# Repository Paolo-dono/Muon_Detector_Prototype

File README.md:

# Muon Detector Prototype
PCB design for the microcontroller subsystem of a muon detector.
- Creator: Paolo de Bruyn
- License: GNU General Public License v3.0

NOTE: Although the name of the project folder is STM32WL55JC_pcb_design, the STM32WL55JC is not the microcontroller that is used in the design. It was used during the initial design, but it has been replaced by the STM32F051R8. The reason why it was not renamed was because all the external component libraries that were added use the absolute filepath, and it would be a mission to change all of them.

## Component availability
All of the components are available from JLCPCB except for a few exceptions.

The GPS module needs an external antenna in order to function properly. Any antenna that has an IPEX MHF connector can be used. One recommendation is the KYOCERA AVX GPS Antenna 1004138 which is available from RS Components.

The banana connectors are sadly not available from JLCPCB but can be procured from DigiKey. It is recommended that the CT3151SP-0 connector is ordered for the ground connector as it is black, and the CT3151-6 is a blue connector which can be used for the supply voltage.

## Using the project
Simply clone the project and open it in KiCAD. The PCB should be in a state where it can already be printed by JLCPCB, but if not, probably only minor changes will have to be made.

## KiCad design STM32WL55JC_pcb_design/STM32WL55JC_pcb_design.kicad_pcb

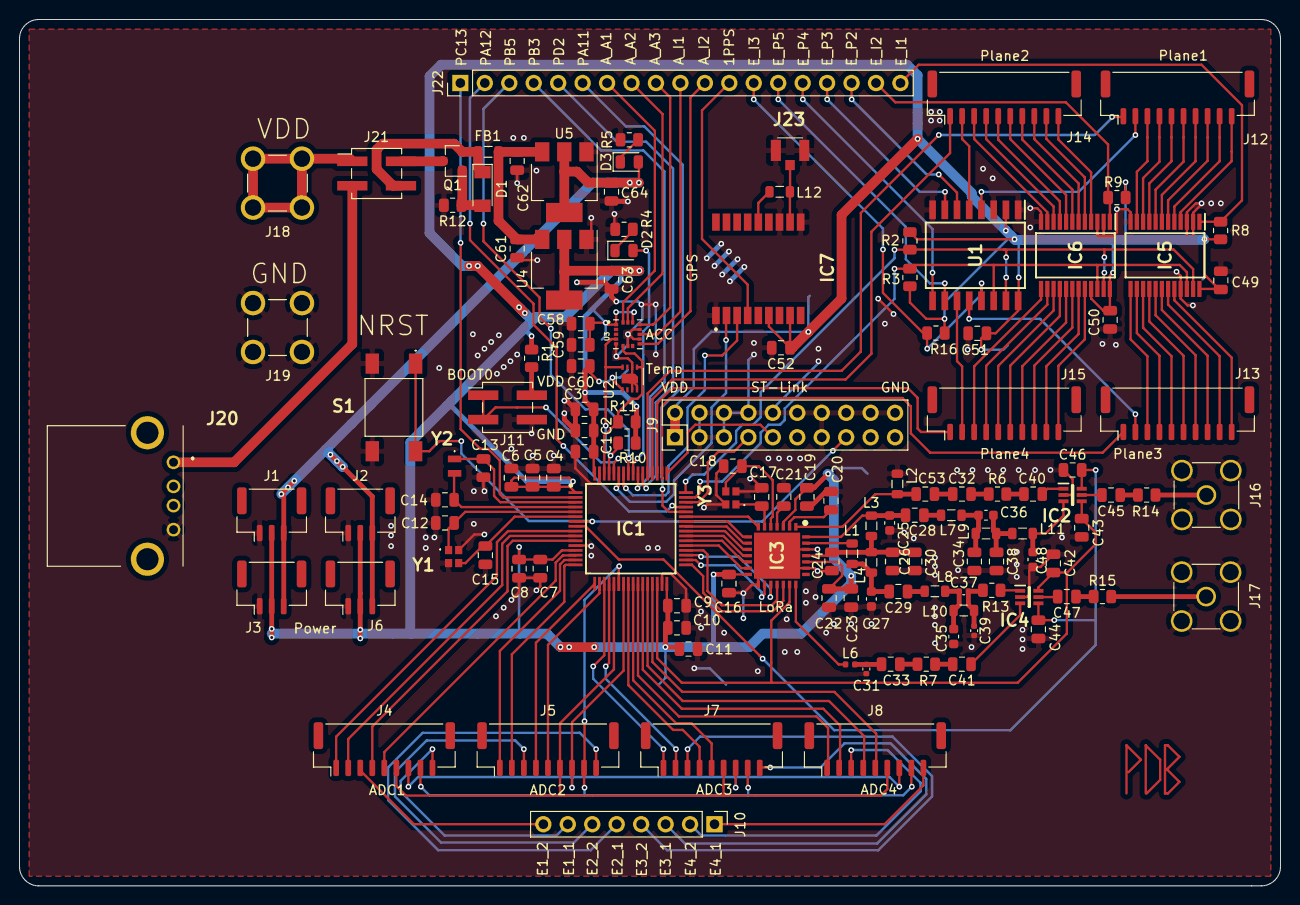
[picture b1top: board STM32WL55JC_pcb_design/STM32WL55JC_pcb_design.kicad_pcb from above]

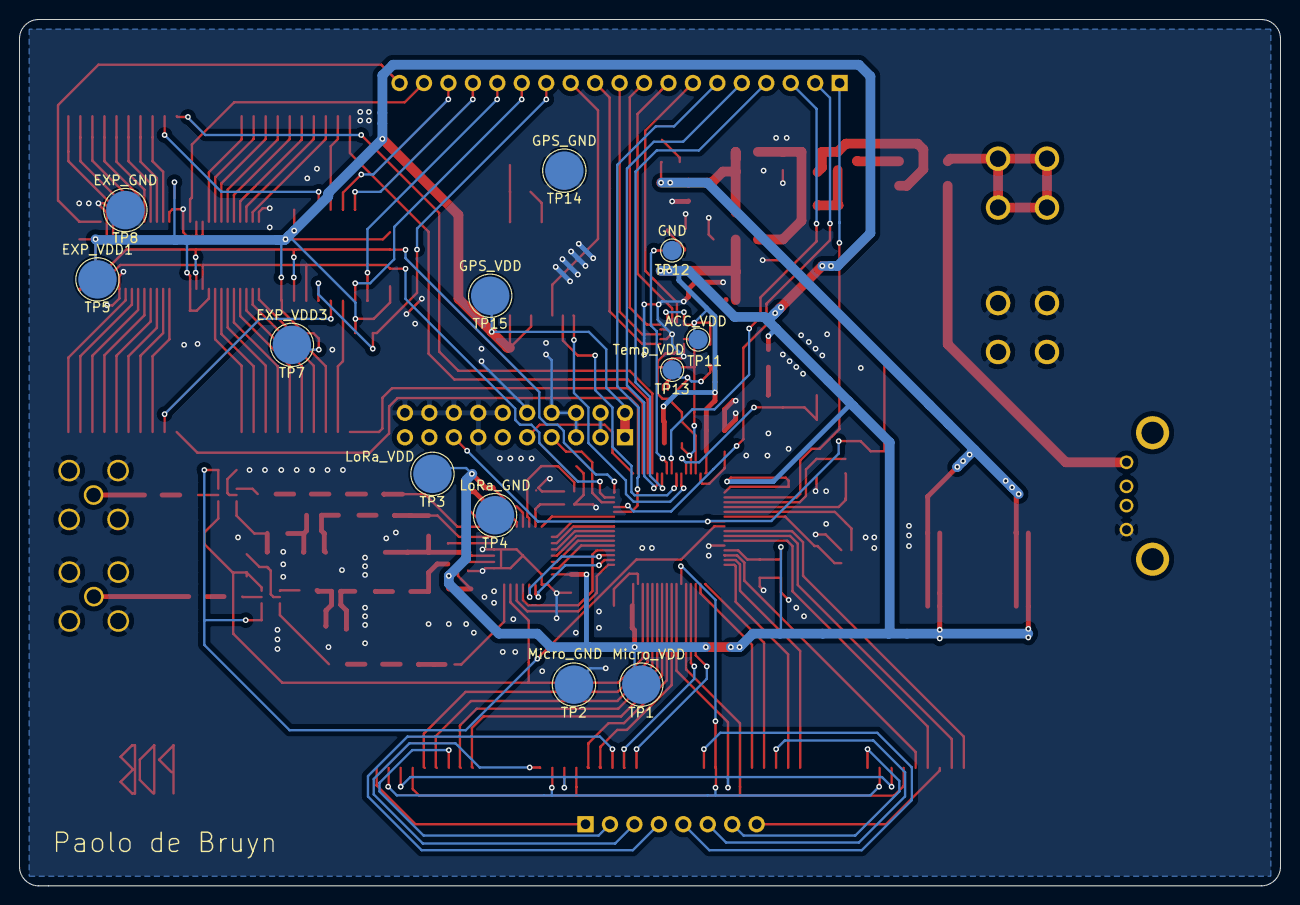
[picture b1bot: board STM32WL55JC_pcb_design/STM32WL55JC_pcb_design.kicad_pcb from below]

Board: 2 copper layers, 131.0 x 90.0 mm, 143 parts (12 on the bottom side), 160 nets.

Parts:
C1, C2, C4, C5, C9, C10, C16, C19, C20, C21, C23, C49, C50, C51, C58, C60: 100nF; C_0805_2012Metric
C3, C6, C11: 4.7uF; C_0805_2012Metric
C7, C24: 10nF; C_0805_2012Metric
C8: 1uF; C_0805_2012Metric
C12, C15, C17, C18: 10pF; C_0805_2012Metric
C13, C14, C34: 15pF; C_0805_2012Metric
C22, C28, C30, C32, C33, C41, C45, C47: 47pF; C_0805_2012Metric
C25, C27, C35: 8.2pF; C_0603_1608Metric
C26: 100pF; C_0805_2012Metric
C29: 22pF; C_0805_2012Metric
C31, C39: 3.3pF; C_0402_1005Metric
C36: 2.7pF; C_0603_1608Metric
C37: 1.5pF; C_0402_1005Metric
C38: 12pF; C_0805_2012Metric
C40: 47nF; C_0805_2012Metric
C42: 4.7pF; C_0603_1608Metric
C43, C44, C46, C48: 1nF; C_0805_2012Metric
C52, C59, C61, C62, C63, C64: 10uF; C_0805_2012Metric
C53: 4.7pF; C_0805_2012Metric
D1: ZMM3V3; D_MiniMELF
D2, D3: LED; LED_0805_2012Metric
FB1: 100@100MHz; L_0805_2012Metric
IC1: STM32F051R8T6; QFP50P1200X1200X160-64N
IC2, IC4: CG2409M2; CKRF2406XS03-C2
IC3: SX1276IMLTRT; QFN65P600X600X100-29N
IC5, IC6: PCF8575TS_1,118; SOP65P775X200-24N
IC7: ATGM336H-5N31; ATGM336H5N31
J1, J2, J3, J6: Conn_01x03; JST_GH_BM03B-GHS-TBT_1x03-1MP_P1.25mm_Vertical
J4, J5, J7, J8: Conn_01x09; JST_GH_BM09B-GHS-TBT_1x09-1MP_P1.25mm_Vertical
J9: Conn_02x10_Odd_Even; PinHeader_2x10_P2.54mm_Vertical
J10: Conn_01x08_Male; PinHeader_1x08_P2.54mm_Vertical
J11, J21: Conn_02x02_Odd_Even; PinHeader_2x02_P2.54mm_Vertical_SMD
J12, J13, J14, J15: Conn_01x10; JST_GH_BM10B-GHS-TBT_1x10-1MP_P1.25mm_Vertical
J16, J17: Conn_Coaxial; SMA_Amphenol_901-144_Vertical
J18, J19: CT3151-2; CALTEST_CT3151-2
J20: USB-A-S-F-B-TH; USBASFBTH
J22: Conn_01x19_Male; PinHeader_1x19_P2.54mm_Vertical
J23: RSP-122811-01; RSP12281101
L1: 2.2nH; L_0805_2012Metric
L2, L11: 18nH; L_0805_2012Metric
L3, L12: 47nH; L_0805_2012Metric
L4: 33nH; L_0805_2012Metric
L6: 10nH; L_0402_1005Metric
L7: 22nH; L_0805_2012Metric
L8: 5.6nH; L_0805_2012Metric
L9: 12nH; L_0805_2012Metric
L10: 4.7nH; L_0805_2012Metric
Q1: AO3401A; SOT-23
R1, R4, R5: 1k; R_0805_2012Metric
R2, R3, R8, R9, R10, R11, R16: 2.2k; R_0805_2012Metric
R6, R7, R13, R14, R15: 0R; R_0805_2012Metric
R12: 100kOhm; R_0805_2012Metric
S1: TL3301AF160QJ
TP1: Micro_VDD; TestPoint_Pad_D4.0mm
TP2: Micro_GND; TestPoint_Pad_D4.0mm
TP3: LoRa_VDD; TestPoint_Pad_D4.0mm
TP4: LoRa_GND; TestPoint_Pad_D4.0mm
TP5: EXP_VDD1; TestPoint_Pad_D4.0mm
TP7: EXP_VDD3; TestPoint_Pad_D4.0mm
TP8: EXP_GND; TestPoint_Pad_D4.0mm
TP11: ACC_VDD; TestPoint_Pad_D2.0mm
TP12: GND; TestPoint_Pad_D2.0mm
TP13: Temp_VDD; TestPoint_Pad_D2.0mm
TP14: GPS_GND; TestPoint_Pad_D4.0mm
TP15: GPS_VDD; TestPoint_Pad_D4.0mm
U1: PCF8574; SOIC127P1032X265-16N
U2: SHT30-DIS; Sensirion_DFN-8-1EP_2.5x2.5mm_P0.5mm_EP1.1x1.7mm
U3: LIS3DHTR; XDCR_LIS3DHTR
U4: AMS1117-3.3; SOT-223-3_TabPin2
U5: AMS1117-5.0; SOT-223-3_TabPin2
Y1, Y3: 32MHz; NX2016SA32MEXS00ACS06465
Y2: 32.768kHz; SC20S125PF20PPM

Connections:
5V: C64.1, D3.2, J1.3, J2.3, J3.3, J6.3, U5.2
+5V: J20.1, J21.3
ACC_ADC1: J22.7, U3.16
ACC_ADC2: J22.8, U3.15
ACC_ADC3: J22.9, U3.13
ACC_INT1: J22.10, U3.11
ACC_INT2: J22.11, U3.9
ADC_CNVST1_1: IC1.11, J4.4
ADC_CNVST1_2: IC1.9, J4.1
ADC_CNVST2_1: IC1.17, J5.4
ADC_CNVST2_2: IC1.15, J5.1
ADC_CNVST3_1: IC1.24, J7.4
ADC_CNVST3_2: IC1.19, J7.1
ADC_CNVST4_1: IC1.28, J8.4
ADC_CNVST4_2: IC1.26, J8.1
ADC_CS1_1: IC1.14, J4.5
ADC_CS1_2: IC1.10, J4.2
ADC_CS2_1: IC1.18, J5.5
ADC_CS2_2: IC1.16, J5.2
ADC_CS3_1: IC1.25, J7.5
ADC_CS3_2: IC1.20, J7.2
ADC_CS4_1: IC1.29, J8.5
ADC_CS4_2: IC1.27, J8.2
ADC_DIN: IC1.23, J4.7, J5.7, J7.7, J8.7
ADC_DOUT: IC1.22, J4.8, J5.8, J7.8, J8.8
ADC_EOC1_1: J4.9, J10.7
ADC_EOC1_2: J4.3, J10.8
ADC_EOC2_1: J5.9, J10.5
ADC_EOC2_2: J5.3, J10.6
ADC_EOC3_1: J7.9, J10.3
ADC_EOC3_2: J7.3, J10.4
ADC_EOC4_1: J8.9, J10.1
ADC_EOC4_2: J8.3, J10.2
ADC_SCLK: IC1.21, J4.6, J5.6, J7.6, J8.6
BOOT0: IC1.60, J11.1, J11.3
ENC1_1: IC5.4, J12.10
ENC1_2: IC5.5, J12.9
ENC1_3: IC5.6, J12.8
ENC1_4: IC5.7, J12.7
ENC2_1: IC5.8, J12.6
ENC2_2: IC5.9, J12.5
ENC2_3: IC5.10, J12.4
ENC2_4: IC5.11, J12.3
ENC3_1: IC6.4, J14.10
ENC3_2: IC6.5, J14.9
ENC3_3: IC6.6, J14.8
ENC3_4: IC6.7, J14.7
ENC4_1: IC6.8, J14.6
ENC4_2: IC6.9, J14.5
ENC4_3: IC6.10, J14.4
ENC4_4: IC6.11, J14.3
ENC5_1: IC5.20, J13.10
ENC5_2: IC5.19, J13.9
ENC5_3: IC5.18, J13.8
ENC5_4: IC5.17, J13.7
ENC6_1: IC5.16, J13.6
ENC6_2: IC5.15, J13.5
ENC6_3: IC5.14, J13.4
ENC6_4: IC5.13, J13.3
ENC7_1: IC6.20, J15.10
ENC7_2: IC6.19, J15.9
ENC7_3: IC6.18, J15.8
ENC7_4: IC6.17, J15.7
ENC8_1: IC6.16, J15.6
ENC8_2: IC6.15, J15.5
ENC8_3: IC6.14, J15.4
ENC8_4: IC6.13, J15.3
ENC_RST_1: J12.2, U1.4
ENC_RST_2: J14.2, U1.5
ENC_RST_3: J13.2, U1.12
ENC_RST_4: J15.2, U1.11
EXP_INT1: IC5.1, J22.19, R8.2
EXP_INT2: IC6.1, J22.18, R9.2
EXP_INT3: J22.13, R16.2, U1.13
EXP_P2: J22.17, U1.6
EXP_P3: J22.16, U1.7
EXP_P4: J22.15, U1.9
EXP_P5: J22.14, U1.10
EXP_SCL: IC1.47, IC5.22, IC6.22, R3.2, U1.14
EXP_SDA: IC1.48, IC5.23, IC6.23, R2.2, U1.15
GNDREF: C1.2, C2.2, C3.2, C4.2, C5.2, C6.2, C7.2, C8.2, C9.2, C10.2, C11.2, C12.2, C13.2, C14.2, C15.2, C16.2, C17.2, C18.2, C19.2, C20.2, C21.2, C22.2, C23.2, C24.2, C25.2, C26.2, C27.2, C30.2, C31.2, C34.2, C35.2, C38.2, C39.2, C42.2, C43.2, C44.2, C46.2, C48.2, C49.2, C50.2, C51.2, C52.2, C58.1, C59.1, C60.2, C61.2, C62.2, C63.2, C64.2, IC1.12, IC1.31, IC1.63, IC2.2, IC3.15, IC3.23, IC3.26, IC3.29, IC4.2, IC5.2, IC5.3, IC5.12, IC5.21, IC6.2, IC6.3, IC6.12, IC7.1, IC7.10, IC7.12, J1.1, J2.1, J3.1, J6.1, J9.3, J9.4, J9.5, J9.6, J9.8, J9.10, J9.12, J9.13, J9.14, J9.16, J9.18, J9.20, J11.4, J16.2, J17.2, J19.1, J19.2, J19.3, J19.4, J20.4, J23.2, J23.3, L2.1, R4.1, R5.2, R12.2, S1.3, S1.4, TP2.1, TP4.1, TP8.1, TP12.1, TP14.1, U1.1, U1.3, U1.8, U2.2, U2.7, U2.8, U2.9, U3.5, U3.7, U3.10, U3.12, U4.1, U5.1, Y1.2, Y1.4, Y3.2, Y3.4
GPS_1PPS: IC7.4, J22.12
LoRa_DO0: IC1.42, IC3.8
LoRa_DO1: IC1.41, IC3.9
LoRa_DO2: IC1.40, IC3.10
LoRa_DO3: IC1.39, IC3.11
LoRa_DO4: IC1.38, IC3.12
LoRa_DO5: IC1.37, IC3.13
LoRa_MISO: IC1.35, IC3.17
LoRa_MOSI: IC1.36, IC3.18
LoRa_NRST: IC1.43, IC3.7
LoRa_NSS: IC1.33, IC3.19
LoRa_RX_EN: C44.1, C46.1, IC1.8, IC2.6, IC4.4
LoRa_SCK: IC1.34, IC3.16
LoRa_TX_EN: C43.1, C48.1, IC1.30, IC2.4, IC3.20, IC4.6
NRST: IC1.7, J9.15, S1.1, S1.2
unnamed: C17.1, IC3.6, Y3.1
unnamed: C18.1, IC3.5, Y3.3
unnamed: C20.1, IC3.2
unnamed: C21.1, IC3.4
unnamed: C24.1, C26.1, C30.1, IC3.25, L3.1, L4.2
unnamed: C25.1, C28.2, IC3.28, L3.2
unnamed: C27.1, C29.2, L1.1, L4.1
unnamed: C28.1, L7.1
unnamed: C29.1, L8.1
unnamed: C31.1, C33.2, L6.2
unnamed: C32.1, R6.1
unnamed: C32.2, C53.1
unnamed: C33.1, R7.1
unnamed: C34.1, C36.2, L7.2, L9.1
unnamed: C35.1, C37.2, L8.2, L10.1
unnamed: C36.1, C38.1, L9.2, L11.1
unnamed: C37.1, C39.1, L10.2, R13.1
unnamed: C40.1, IC2.1
unnamed: C40.2, R6.2
unnamed: C41.1, IC4.3
unnamed: C41.2, R7.2
unnamed: C42.1, IC2.3, L11.2
unnamed: C45.1, R14.1
unnamed: C45.2, IC2.5
unnamed: C47.1, R15.1
unnamed: C47.2, IC4.5
unnamed: C53.2, IC3.1, L2.2
unnamed: C61.1, C62.1, FB1.1, U4.3, U5.3
unnamed: D1.1, FB1.2, J21.4, Q1.2
unnamed: D1.2, Q1.1, R12.1
unnamed: D2.1, R4.2
unnamed: D2.2, IC1.56
unnamed: D3.1, R5.1
unnamed: IC3.21, L6.1
unnamed: IC3.27, L1.2
unnamed: IC4.1, R13.2
unnamed: IC7.11, J23.1, L12.2
unnamed: IC7.14, L12.1
unnamed: J11.2, R1.2
unnamed: J16.1, R14.2
unnamed: J17.1, R15.2
unnamed: J18.1, J18.2, J18.3, J18.4, J21.1
unnamed: J21.2, Q1.3
OR1: IC1.53, J12.1
OR2: IC1.52, J14.1
OR3: IC1.50, J13.1
OR4: IC1.51, J15.1
OSC32_IN: C13.1, IC1.3, Y2.1
OSC32_OUT: C14.1, IC1.4, Y2.2
OSC_IN: C12.1, IC1.5, Y1.1
OSC_OUT: C15.1, IC1.6, Y1.3
PA11: IC1.44, J22.6
PA12: IC1.45, J22.2
PB3: IC1.55, J22.4
PB5: IC1.57, J22.3
PC13: IC1.2, J22.1
PD2: IC1.54, J22.5
RX: IC1.58, IC7.3
SCL: IC1.61, R10.2, U2.4, U3.4
SDA: IC1.62, R11.2, U2.1, U3.6
SWCLK: IC1.49, J9.9
SWDIO: IC1.46, J9.7
TX: IC1.59, IC7.2
VDD: C1.1, C2.1, C3.1, C4.1, C5.1, C6.1, C7.1, C8.1, C9.1, C10.1, C11.1, C16.1, C19.1, C22.1, C23.1, C49.1, C50.1, C51.1, C52.1, C58.2, C59.2, C60.1, C63.1, IC1.1, IC1.13, IC1.32, IC1.64, IC3.3, IC3.14, IC3.24, IC5.24, IC6.21, IC6.24, IC7.6, IC7.8, J1.2, J2.2, J3.2, J6.2, J9.1, J9.2, R1.1, R2.1, R3.1, R8.1, R9.1, R10.1, R11.1, R16.1, TP1.1, TP3.1, TP5.1, TP7.1, TP11.1, TP13.1, TP15.1, U1.2, U1.16, U2.5, U3.1, U3.14, U4.2

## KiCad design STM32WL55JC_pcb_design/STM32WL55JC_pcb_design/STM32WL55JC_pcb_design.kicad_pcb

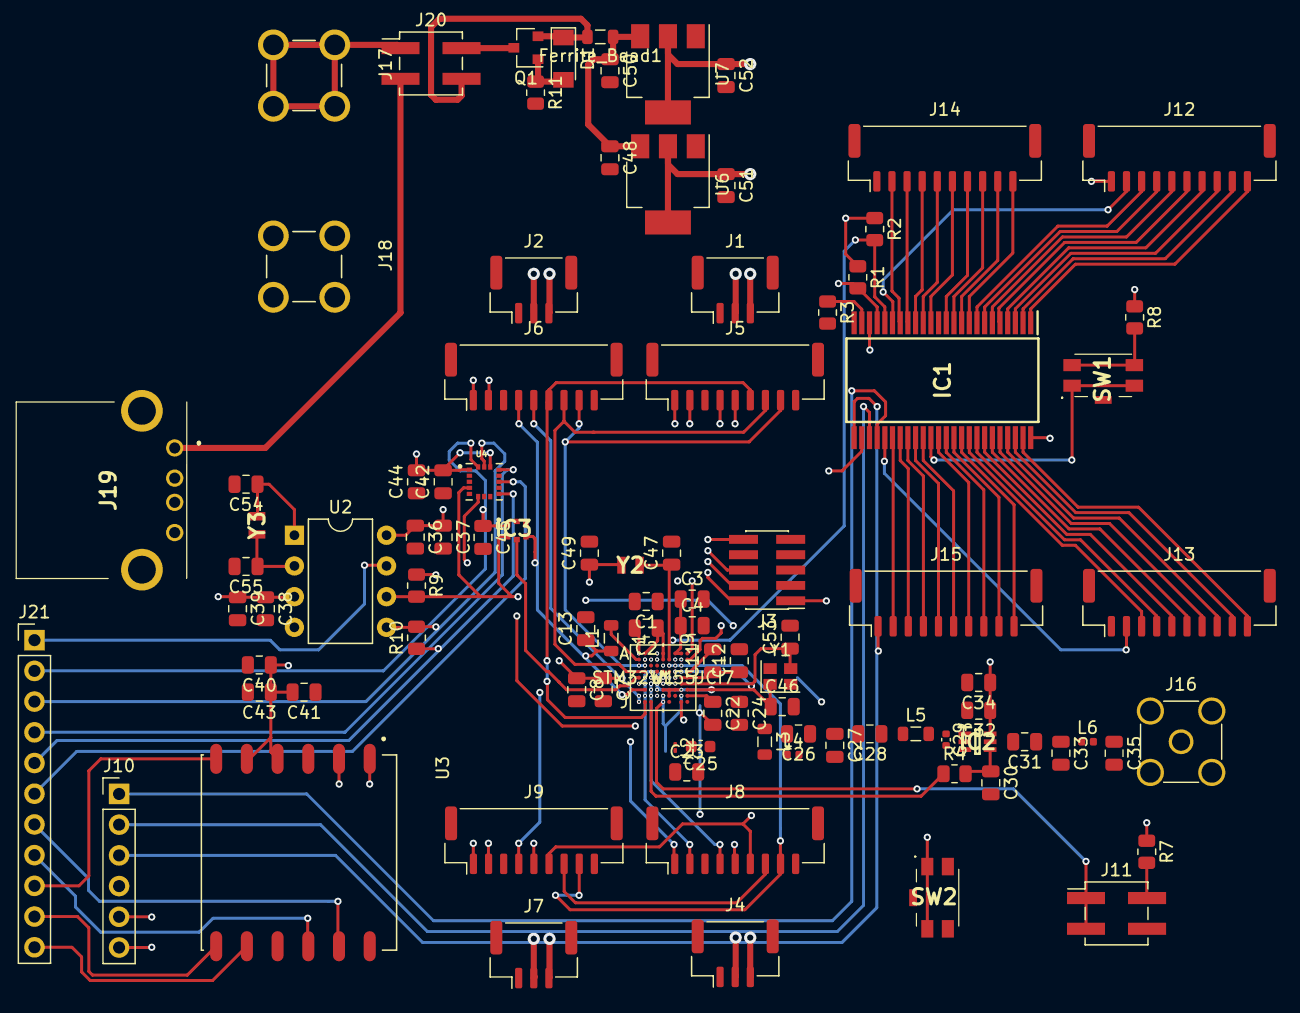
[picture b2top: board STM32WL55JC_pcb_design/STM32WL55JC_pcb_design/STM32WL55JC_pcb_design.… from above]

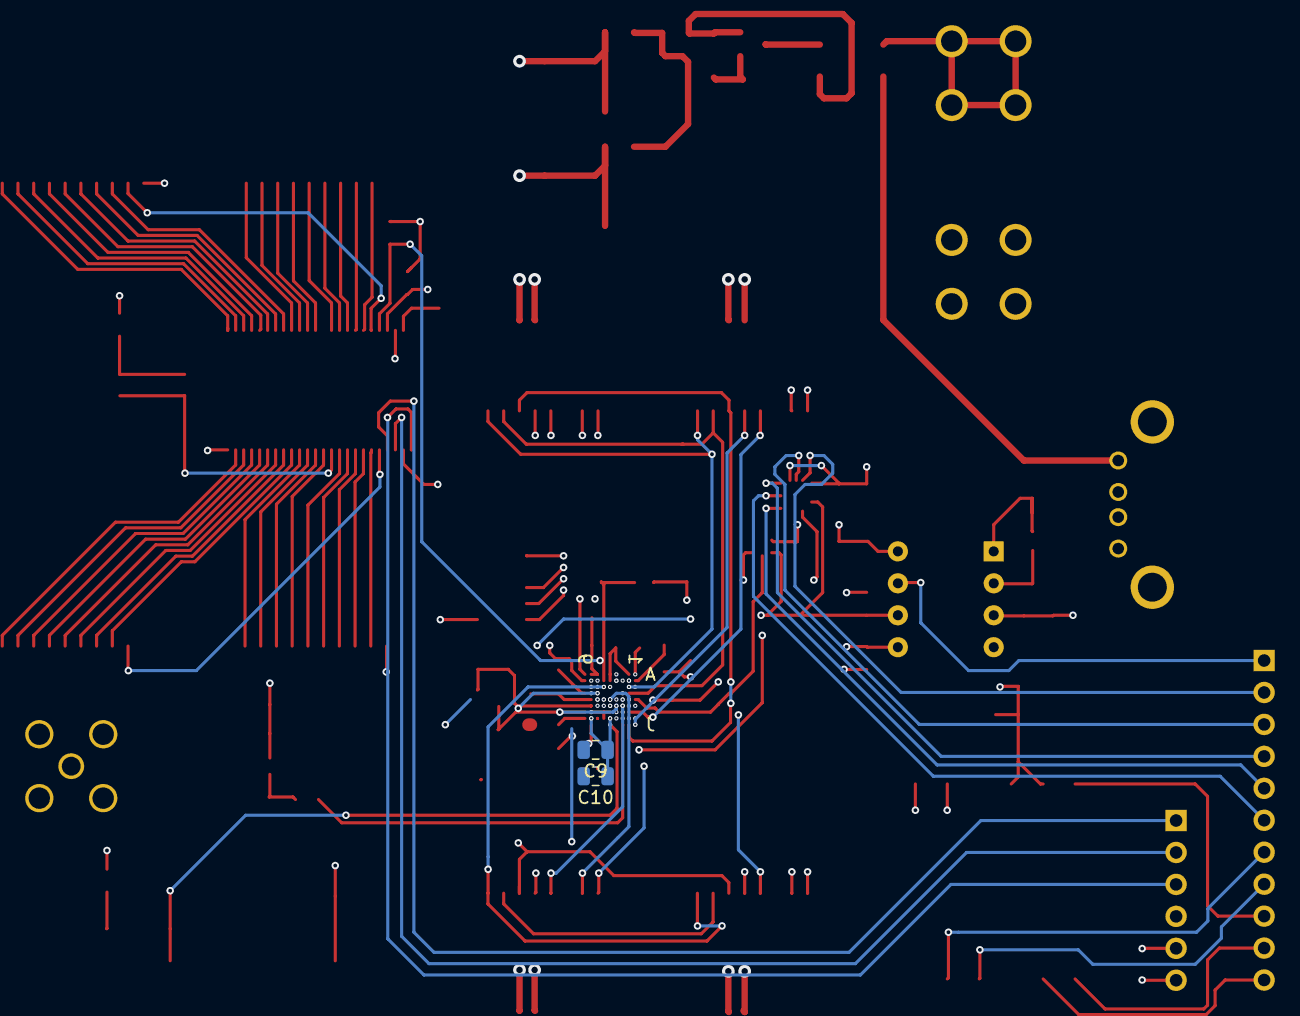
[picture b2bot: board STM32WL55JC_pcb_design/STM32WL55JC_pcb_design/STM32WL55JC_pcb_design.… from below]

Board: 4 copper layers, 98 parts (2 on the bottom side), 126 nets.

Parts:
C1, C2, C3, C4, C7, C8, C9, C10, C11, C12, C32, C36, C38, C40, C41, C42, C45: 100nF; C_0805_2012Metric
C13: 470nF; C_0805_2012Metric
C22: 47nF; C_0805_2012Metric
C23: 1.8pF; C_0805_2012Metric
C24: 47pF; C_0805_2012Metric
C25: 2.4pF; C_0603_1608Metric
C26, C33, C35: 3.3pF; C_0805_2012Metric
C27: 5.6pF; C_0805_2012Metric
C28, C31: 39pF; C_0805_2012Metric
C29: 2.2pF; C_0402_1005Metric
C30: 1nF; C_0805_2012Metric
C34, C37, C39, C43, C44, C48, C50, C51, C52: 10uF; C_0805_2012Metric
C46, C53: 2.2pF; C_0805_2012Metric
C47, C49, C54, C55: 15pF; C_0805_2012Metric
D1: ZMM3V3; D_MiniMELF
Ferrite_Bead1: 100@100MHz; L_0805_2012Metric
IC1: CY8C9540A-24PVXIT; SOP64P1035X279-48N
IC2: PE4259; SOT65P210X110-6N
IC3: HTS221TR
J1, J2, J4, J7: Conn_01x03; JST_GH_BM03B-GHS-TBT_1x03-1MP_P1.25mm_Vertical
J3: Conn_02x05_Odd_Even; PinHeader_2x05_P1.27mm_Vertical_SMD
J5, J6, J8, J9: Conn_01x09; JST_GH_BM09B-GHS-TBT_1x09-1MP_P1.25mm_Vertical
J10: Conn_01x06_Male; PinHeader_1x06_P2.54mm_Vertical
J11, J20: Conn_02x02_Odd_Even; PinHeader_2x02_P2.54mm_Vertical_SMD
J12, J13, J14, J15: Conn_01x10; JST_GH_BM10B-GHS-TBT_1x10-1MP_P1.25mm_Vertical
J16: Conn_Coaxial; SMA_Amphenol_901-144_Vertical
J17, J18: CT3151-2; CALTEST_CT3151-2
J19: USB_A; USBASFBTH
J21: Conn_01x11_Male; PinHeader_1x11_P2.54mm_Vertical
L1: 15uH; L_0805_2012Metric
L2: 15nH; L_01005_0402Metric
L3: 47nH; L_0805_2012Metric
L4: 2.5nH; L_0402_1005Metric
L5: 4.7nH; L_0805_2012Metric
L6: 9.1nH; L_0402_1005Metric
Q1: AO3401A; SOT-23
R1, R2, R9, R10: 2.2k; R_0805_2012Metric
R3: 200; R_0805_2012Metric
R4: 100; R_0805_2012Metric
R7, R8: 1k; R_0805_2012Metric
R11: 100kOhm; R_0805_2012Metric
SW1, SW2: SW_MEC_5E; EVQP2V02W
U1: STM32WL55JCI7
U2: DS1307+; DIP-8_W7.62mm
U3: L80-M39; XCVR_L80-M39
U4: LIS3DHTR; XDCR_LIS3DHTR
U6: AMS1117-3.3; SOT-223-3_TabPin2
U7: AMS1117-5.0; SOT-223-3_TabPin2
Y1: 32MHz; Oscillator_SMD_SeikoEpson_SG210-4Pin_2.5x2.0mm
Y2, Y3: 32.768kHz; SC20S125PF20PPM

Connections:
5V: C36.1, C37.1, C52.1, J1.3, J2.3, J4.3, J7.3, U2.8, U7.2
+5V: J19.1, J20.3
ACC_ADC1: J21.2, U4.16
ACC_ADC2: J21.3, U4.15
ACC_ADC3: J21.4, U4.13
ACC_INT1: J21.6, U4.11
ACC_INT2: J21.5, U4.9
ADC_CNVST1_1: J5.4, U1.H4
ADC_CNVST1_2: J5.1, U1.H3
ADC_CNVST2_1: J6.4, U1.G2
ADC_CNVST2_2: J6.1, U1.F6
ADC_CNVST3_1: J8.4, U1.F3
ADC_CNVST3_2: J8.1, U1.F2
ADC_CNVST4_1: J9.4, U1.F1
ADC_CNVST4_2: J9.1, U1.E7
ADC_CS1_1: J5.5, U1.B3
ADC_CS1_2: J5.2, U1.D8
ADC_CS2_1: J6.5, U1.J1
ADC_CS2_2: J6.2, U1.A9
ADC_CS3_1: J8.5, U1.C4, U1.G4
ADC_CS3_2: J8.2, U1.E5
ADC_CS4_1: J9.5, U1.E6
ADC_CS4_2: J9.2, U1.C3
ADC_DIN1: J5.7, J6.7, U1.D2
ADC_DIN2: J8.7, J9.7, U1.D5
ADC_DOUT1: J5.8, J6.8, U1.C2
ADC_DOUT2: J8.8, J9.8, U1.C6
ADC_SCLK1: J5.6, J6.6, U1.J2
ADC_SCLK2: J8.6, J9.6, U1.D7
ENC1_1: IC1.1, J12.10
ENC1_2: IC1.2, J12.9
ENC1_3: IC1.3, J12.8
ENC1_4: IC1.4, J12.7
ENC2_1: IC1.5, J12.6
ENC2_2: IC1.6, J12.5
ENC2_3: IC1.7, J12.4
ENC2_4: IC1.8, J12.3
ENC3_1: IC1.9, J14.10
ENC3_2: IC1.10, J14.9
ENC3_3: IC1.11, J14.8
ENC3_4: IC1.12, J14.7
ENC4_1: IC1.14, J14.6
ENC4_2: IC1.15, J14.5
ENC4_3: IC1.16, J14.4
ENC4_4: IC1.17, J14.3
ENC5_1: IC1.47, J13.10
ENC5_2: IC1.46, J13.9
ENC5_3: IC1.45, J13.8
ENC5_4: IC1.44, J13.7
ENC6_1: IC1.43, J13.6
ENC6_2: IC1.42, J13.5
ENC6_3: IC1.41, J13.4
ENC6_4: IC1.40, J13.3
ENC7_1: IC1.39, J15.10
ENC7_2: IC1.38, J15.9
ENC7_3: IC1.37, J15.8
ENC7_4: IC1.36, J15.7
ENC8_1: IC1.34, J15.6
ENC8_2: IC1.33, J15.5
ENC8_3: IC1.32, J15.4
ENC8_4: IC1.31, J15.3
ENC_RST_1: IC1.19, J12.2
ENC_RST_2: IC1.18, J14.2
ENC_RST_3: IC1.29, J13.2
ENC_RST_4: IC1.30, J15.2
EXP_0: IC1.28, J10.1
EXP_1: IC1.27, J10.2
EXP_2: IC1.25, J10.3
EXP_3: IC1.22, J10.4
EXP_INT: IC1.26, U1.F4
EXP_SCL: IC1.20, R2.2, U1.B4
EXP_SDA: IC1.21, R1.2, U1.B9
GNDREF: C1.2, C2.2, C3.2, C4.2, C7.2, C8.2, C9.2, C10.2, C11.2, C12.2, C13.2, C22.2, C23.2, C24.2, C27.2, C29.2, C30.2, C32.2, C33.2, C34.2, C35.2, C36.2, C37.2, C38.2, C39.2, C40.2, C41.1, C42.1, C43.2, C44.1, C45.2, C46.2, C47.2, C48.2, C49.2, C50.2, C51.2, C52.2, C53.2, C54.2, C55.2, IC1.13, IC1.24, IC2.2, IC3.5, J1.1, J2.1, J3.3, J3.5, J3.9, J4.1, J7.1, J11.4, J16.2, J18.1, J18.2, J18.3, J18.4, J19.4, R3.2, R11.2, SW2.2, SW2.4, U1.A1, U1.B7, U1.D9, U1.E3, U1.G5, U1.G6, U1.G7, U1.G8, U1.H6, U2.4, U3.3, U3.12, U4.5, U4.10, U4.12, U6.1, U7.1, Y1.2, Y1.4
GPS_1PPS: J21.9, U3.6
GPS_AADET_N: J21.11, U3.8
GPS_EX_ANT: J21.7, U3.11
GPS_RESET: J21.8, U3.10
GPS_TIMER: J21.10, U3.7
NRST: J3.10, SW2.1, SW2.3, U1.F5
unnamed: C25.1, IC2.3
unnamed: C26.1, C27.1, C28.2, L4.2
unnamed: C28.1, L5.1
unnamed: C29.1, IC2.1, L5.2
unnamed: C30.1, IC2.4, R4.2
unnamed: C31.1, C33.1, L6.1
unnamed: C31.2, IC2.5
unnamed: C35.1, J16.1, L6.2
unnamed: C48.1, C50.1, Ferrite_Bead1.1, U6.3, U7.3
unnamed: C54.1, U2.1, Y3.1
unnamed: C55.1, U2.2, Y3.2
unnamed: D1.1, Ferrite_Bead1.2, J20.4, Q1.2
unnamed: D1.2, Q1.1, R11.1
unnamed: IC1.23, R3.1
unnamed: IC1.35, SW1.1, SW1.3
unnamed: J11.1, J11.3, U1.J5
unnamed: J11.2, R7.2
unnamed: J17.1, J17.2, J17.3, J17.4, J20.1
unnamed: J20.2, Q1.3
unnamed: L1.2, U1.B1
unnamed: R8.2, SW1.2, SW1.4
OR1: J12.1, U1.C7
OR2: J14.1, U1.D4
OR3: J13.1, U1.D6
OR4: J15.1, U1.G3
OSC32_IN: C47.1, U1.B6, Y2.1
OSC32_OUT: C49.1, U1.C5, Y2.2
OSC_IN: C46.1, U1.G9, Y1.1
OSC_OUT: C53.1, U1.F8, Y1.3
PC5: J10.5, U1.E4
RFI_N: C25.2, L2.1, U1.H7
RFI_P: C23.1, L2.2, U1.J6
RFO_HP: C26.2, L3.2, L4.1, U1.J9
RFO_LP: J10.6, U1.J8
RF_CTRL: R4.1, U1.J3
RTC_SQW: J21.1, U2.7
RX: U1.H2, U3.1
SCL: IC3.2, R9.2, U1.D3, U2.6, U4.4
SDA: IC3.4, R10.2, U1.C8, U2.5, U4.6
SWCLK: J3.4, U1.A4
SWDIO: J3.2, U1.B8
SWO: J3.6, U1.C1
TX: U1.H1, U3.2
TempHumid_DRDY: IC3.3, U1.E1
VBAT: C1.1, C2.1, C3.1, C4.1, C7.1, C8.1, C9.1, C10.1, C11.1, C12.1, C32.1, C34.1, C38.1, C39.1, C40.1, C41.2, C42.2, C43.1, C44.2, C45.1, C51.1, IC1.48, IC2.6, IC3.1, J1.2, J2.2, J3.1, J4.2, J7.2, R1.1, R2.1, R7.1, R8.1, R9.1, R10.1, U1.A2, U1.A5, U1.A7, U1.A8, U1.B5, U1.E2, U1.E8, U1.E9, U1.H5, U1.H8, U2.3, U3.4, U3.5, U4.1, U4.14, U6.2
VDDRF_1V55: C13.1, L1.1, U1.B2, U1.F7
VR_PA: C22.1, C24.1, L3.1, U1.H9

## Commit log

2021-09-01 First commit of PCB design
2021-09-03 First pcb commit
2021-09-07 Complete first version - todo: rf pins
2021-09-14 Add temperature and humidty sensor, add rf connections
2021-09-14 Add missing cap on LoRa.sch
2021-09-14 Add RTC
2021-09-29 Finish RF matching network
2021-09-30 Update ADC section to work with MAX11635
2021-09-30 Finish component selection and footprint assignment
2021-10-05 Initial pcb layout
2021-10-06 Finished component placement
2021-10-06 Only micro left to be routed
2021-10-07 Add some microcontroller routing
2021-10-17 Finish new design schematic
2021-10-18 Initial pcb layout and routing
2021-10-19 Finish pcb routing
2021-10-22 Remove acid traps, make vias the same size, and improve wire spacing
2021-10-26 Change devices to available ones from JLC
2021-10-26 Add copper fill and edge cuts
2021-10-27 Finish routing
2021-10-27 Finish silk screen
2021-11-07 Final push
2021-11-07 Add README
2021-11-07 Correct copper fill
2021-11-22 Add final report

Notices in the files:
parts and their libraries:
Copyright 2021 Accelerated Designs. All rights reserved.
